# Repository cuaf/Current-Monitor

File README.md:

INA196 Current Sensor
======================

Provides current and voltage measurements based on the voltage drop over a low resistance shunt resistor (e.g. 1 milliohm). 
Small boards arriving soon, cheap to use and make from TI's generous sample offers.

We can use these to measure the motor curent, and probably the avionics power supply too.

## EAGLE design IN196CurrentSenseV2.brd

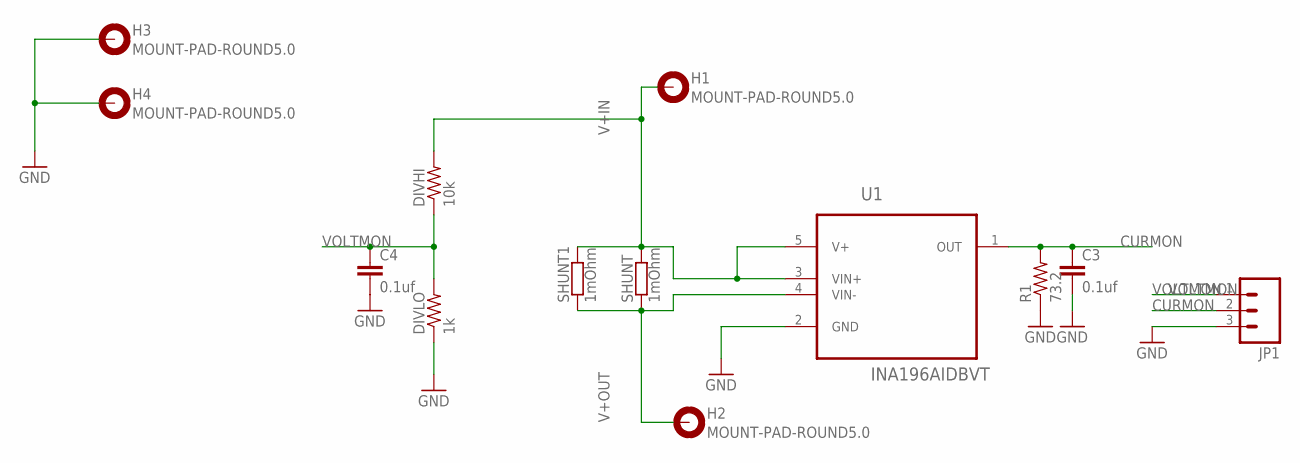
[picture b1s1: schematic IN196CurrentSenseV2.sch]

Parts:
C3, C4: 0.1uf; 0603-CAP
DIVHI: 10k; 0603-RES
DIVLO: 1k; 0603-RES
H1, H2, H3, H4: MOUNT-PAD-ROUND5.0; 5,0-PAD
JP1: M03LONGPADS; 1X03_LONGPADS
R1: 73.2; 0603-RES
SHUNT, SHUNT1: 1mOhm; SMS-0
U1: INA196AIDBVT; SOT95P280X145-5N

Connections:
CURMON: C3.1, JP1.2, R1.2, U1.1 (OUT)
GND: C3.2, C4.2, DIVLO.1, H3.B5, H4.B5, JP1.3, R1.1, U1.2 (GND)
V+IN: DIVHI.2, H1.B5, SHUNT.1, SHUNT1.1, U1.3 (VIN+), U1.5 (V+)
V+OUT: H2.B5, SHUNT.2, SHUNT1.2, U1.4 (VIN-)
VOLTMON: C4.1, DIVHI.1, DIVLO.2, JP1.1

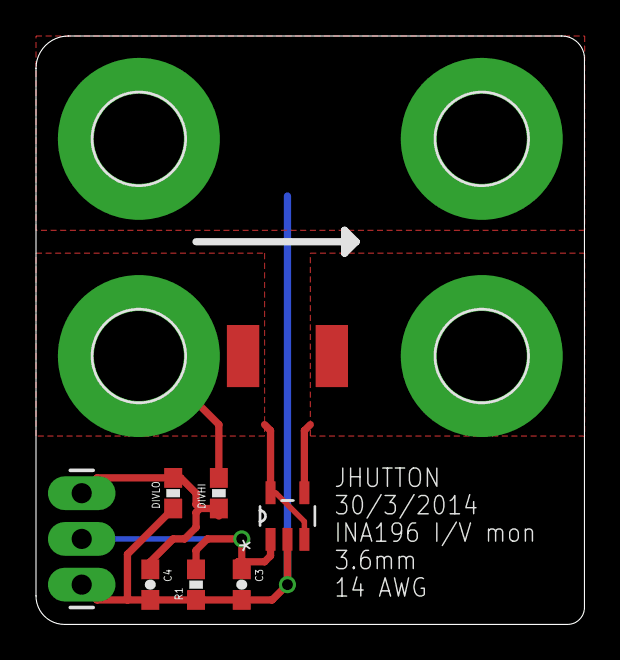
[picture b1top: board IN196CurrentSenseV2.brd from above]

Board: 2 copper layers, 30.5 x 32.7 mm, 13 parts (1 on the bottom side), 5 nets.

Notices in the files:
parts and their libraries:
SparkFun-Capacitors: Licensing: CC v3.0 Share-Alike You are welcome to use this library for commercial purposes.
